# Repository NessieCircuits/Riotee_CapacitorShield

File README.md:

# Riotee Capacitor Shield

The capacitor panel shield plugs into the headers of the [Riotee board](https://github.com/NessieCircuits/Riotee_Board). It allows flexibly adding more capacitance to your device. An 8-position switch is used to selectively connect additional capacitors ranging from tiny ceramics to large supercapacitors.

Latest design files:

 - [Schematics](https://www.riotee.nessie-circuits.de/artifacts/capacitor_shield/latest/schematics.pdf)
 - [Layout](https://www.riotee.nessie-circuits.de/artifacts/capacitor_shield/latest/pcb.pdf)
 - [Rendering](https://www.riotee.nessie-circuits.de/artifacts/capacitor_shield/latest/3drendering.png "Riotee capacitor shield")
 - [Gerber](https://www.riotee.nessie-circuits.de/artifacts/capacitor_shield/latest/gerber.zip)
 - [BOM](https://www.riotee.nessie-circuits.de/artifacts/capacitor_shield/latest/bom.csv)

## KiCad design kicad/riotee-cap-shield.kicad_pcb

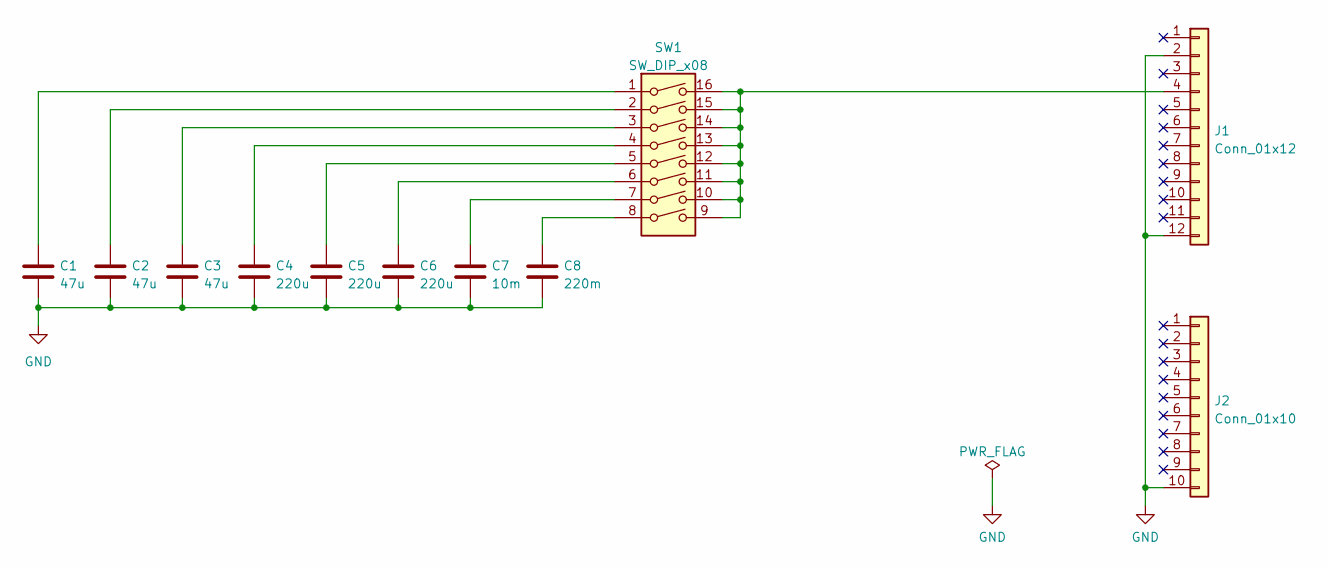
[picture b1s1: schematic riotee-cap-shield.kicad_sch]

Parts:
C1, C2, C3: 47u; C_0805_2012Metric; MPN GRM21BR61A476ME15K
C4, C5, C6: 220u; C_1206_3216Metric; MPN GRM31CR60J227ME11K
C7: 10m; KM_FG0H103ZF; MPN FG0H103ZF
C8: 220m; KM_FG0H103ZF; MPN FGH0H224ZF
J1: Conn_01x12; PinSocket_1x12_P2.54mm_Vertical; MPN PRT-14322
J2: Conn_01x10; PinSocket_1x10_P2.54mm_Vertical; MPN PRT-11376
SW1: SW_DIP_x08; TE_1-1825058-9; MPN 1-1825058-9

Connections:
GND: C1.2, C2.2, C3.2, C4.2, C5.2, C6.2, C7.2, C8.2, J1.2, J1.12, J2.10
unnamed: C1.1, SW1.1
unnamed: C2.1, SW1.2
unnamed: C3.1, SW1.3
unnamed: C4.1, SW1.4
unnamed: C5.1, SW1.5
unnamed: C6.1, SW1.6
unnamed: C7.1, SW1.7
unnamed: C8.1, SW1.8
unnamed: J1.4, SW1.9, SW1.10, SW1.11, SW1.12, SW1.13, SW1.14, SW1.15, SW1.16

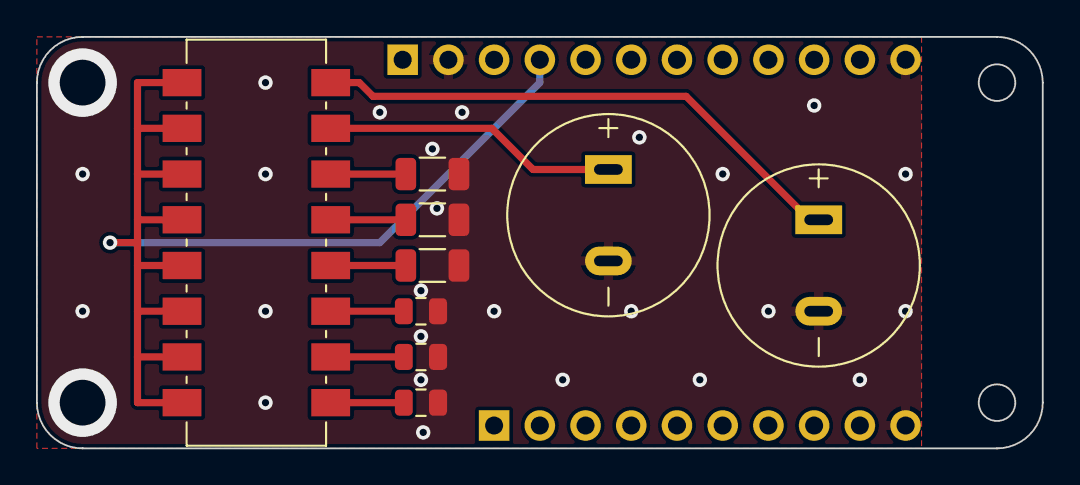
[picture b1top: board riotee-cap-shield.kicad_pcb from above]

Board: 2 copper layers, 55.9 x 22.9 mm, 11 parts (0 on the bottom side), 10 nets.

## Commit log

2023-01-19 add readme
2023-02-09 switch to stacking header 3d models
2023-02-24 add missing license
2023-02-24 add MPNs in schematics
2023-04-14 add conformity marks and refine BOM
2023-04-28 migrate project to kicad 7
2023-04-28 fix header location
2023-04-28 update library
2023-04-28 add kikit configuration for production panel
2023-04-28 add kicad ERC/DRC github action
2023-04-28 make ERC happy with power flag
2023-04-28 rename kibot build workflow
2024-06-26 update to kicad 8
2024-06-26 increase panel frame width
2024-06-26 update kibot action versions
2024-10-15 generate bom and gerber in github workflow with kibot
2024-10-15 update github action versions
